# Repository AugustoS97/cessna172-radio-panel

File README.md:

# cessna-radio-panel

Radio panel for COM or NAV for a Cessna 172 to use with MSFS2020, XPlane and Prepar3D using the software MobiFlight.

# Repo contents

## Cessna-radio-stack-pcb
This folder contents the PCB design for the radio module. The design is the same for COM and NAV, it only changes on the frame. This PCB needs to be connected to the Arduino Mega using the Mega-pro-mini module designed in this repository. There is a GERBER folder to send the design to JLCPCB (www.jlcpcb.com) or you can ask me to buy it finished (augustosamuelhdezmartin@gmail.com).

To make this PCB you need this components (you can find the list in cessna172-radio-panel/Cesna-Radio-Stack-pcb/Docs/Cesna_Radio_Stack.csv):
- 4x Display 7 segments 0.36" 1 bit Common Cathode red (https://www.aliexpress.com/item/1005001852229452.html?spm=a2g0o.cart.0.0.44e13c00yVY6Ir&mp=1)
- 2x Display 7 segments 0.36" 4 bit Common Cathode red AS3161 (https://www.aliexpress.com/item/32673704841.html?spm=a2g0o.cart.0.0.44e13c00yVY6Ir&mp=1).
- 2x Rottary Encoder EC11 (https://es.aliexpress.com/item/1005002931777351.html?spm=a2g0o.cart.0.0.44e13c00yVY6Ir&mp=1) 
- 1x Button 8x8 (https://www.aliexpress.com/item/32467872702.html?spm=a2g0o.cart.0.0.44e13c00yVY6Ir&mp=1)
- 2x MAX7219 DIP24 (https://www.aliexpress.com/item/32874536319.html?spm=a2g0o.cart.0.0.44e13c00yVY6Ir&mp=1)
- 1x PinHeader 2x36 pins (https://www.aliexpress.com/item/33004522737.html?spm=a2g0o.cart.0.0.44e13c00yVY6Ir&mp=1)
- 8x 1k Resistor THT
- 7x 10nF Ceramic Capacitor THT
- 2x 150nF Ceramic Capacitor THT
- 2x 22uF Electrolitic Capcitor 16V

## Mega2560-pro-mini-radio
This folder contents the PCB design for the microcontroller. The design connects 2 NAV modules, 2 COM modules or 1 NAv and 1 COM modules. There is a GERBER folder to send the design to JLCPCB (www.jlcpcb.com) or you can ask me to buy it finished (augustosamuelhdezmartin@gmail.com).

To make this PCB you need this components (you can find the list in cessna172-radio-panel/Mega2560-pro-mini-radio/docs/Mega2560-pro-mini-radio.csv):
- 1x Mega 2650 Pro mini (https://www.aliexpress.com/item/1005001798708448.html?spm=a2g0o.cart.0.0.44e13c00yVY6Ir&mp=1)
- 3x PinHeader male 2x36 pins 2.54 mm (https://www.aliexpress.com/item/32993182990.html?spm=a2g0o.cart.0.0.44e13c00yVY6Ir&mp=1)
- 3x PinHeader Female 1x40 pins 2.54mm (https://www.aliexpress.com/item/32993182990.html?spm=a2g0o.cart.0.0.44e13c00yVY6Ir&mp=1)
- 2x IDC 2x20 pins 2.54mm Cable (https://www.aliexpress.com/item/33029492417.html?spm=a2g0o.cart.0.0.44e13c00yVY6Ir&mp=1): One for each module

## Frame Design
This folders contents the FreeCAD design for the exterior panel. It is based on the c172-xpndr design (https://github.com/kkr0kk/c172-xpndr), so it must be use with this Transponder and AutoPilot modules.

Also the 3D model are available in STL folder, so you can print this panels with 2 colors or you can also contact me to buy a finished panel (augustosamuelhdezmartin@gmail.com).

## Assembly 
Finallly, the COM panel is assembly as shown in the next picture.

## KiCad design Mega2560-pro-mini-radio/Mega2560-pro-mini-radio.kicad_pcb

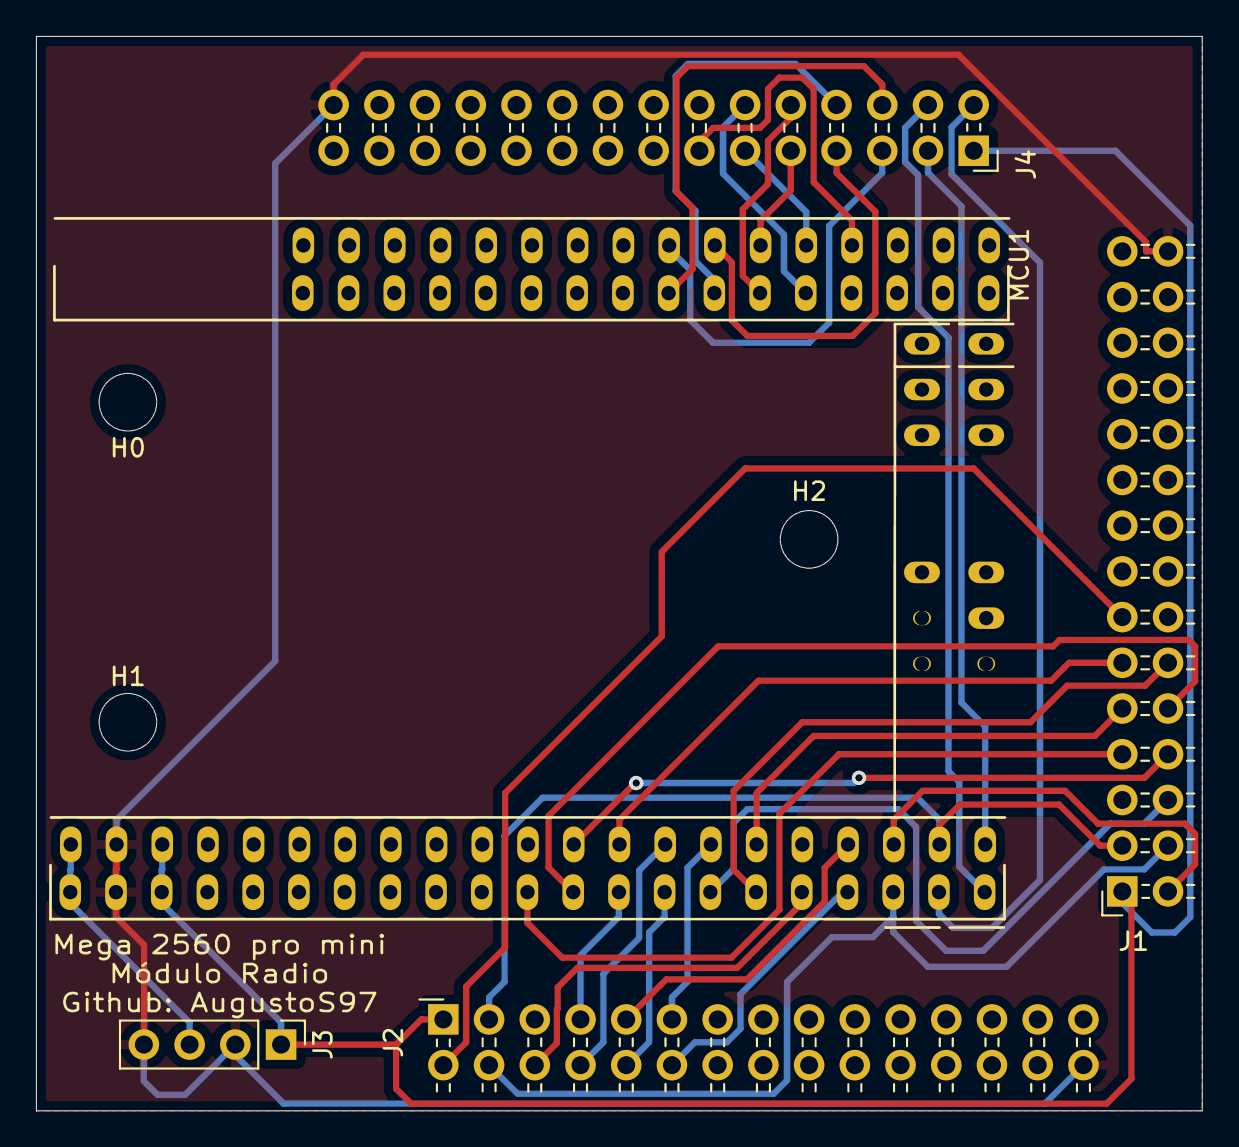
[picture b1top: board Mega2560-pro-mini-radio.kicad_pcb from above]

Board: 2 copper layers, 64.8 x 59.7 mm, 8 parts (0 on the bottom side), 33 nets.

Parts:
H0, H1, H2: MountingHole_3.2mm_M3
J1: COM_CONN; PinSocket_2x15_P2.54mm_Horizontal
J2: NAV_CONN; PinSocket_2x15_P2.54mm_Horizontal
J3: Power_Conn; PinHeader_1x04_P2.54mm_Vertical
J4: SW_CONN; PinSocket_2x15_P2.54mm_Horizontal
MCU1: Mega_Embebido; MEGA_Embebido

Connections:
+5V: J1.1, J2.1, J3.1, J4.1, MCU1.5, MCU1.6
ADF: J4.9, MCU1.53
AUX: J4.10, MCU1.54
A_COM_ENC_KHZ: J1.7, MCU1.22
A_COM_ENC_MHZ: J1.10, MCU1.24
A_NAV_ENC_KHZ: J2.7, MCU1.26
A_NAV_ENC_MHZ: J2.10, MCU1.28
BOTH: J4.4, MCU1.42
B_COM_ENC_KHZ: J1.8, MCU1.23
B_COM_ENC_MHZ: J1.11, MCU1.25
B_NAV_ENC_KHZ: J2.8, MCU1.27
B_NAV_ENC_MHZ: J2.11, MCU1.29
CLK: J1.3, J2.3, MCU1.39
COM1: J4.2, MCU1.40
COM2: J4.3, MCU1.41
COM_SWAP: J1.6, MCU1.30
CS_MAX: J1.4, J2.4, MCU1.38
DIN: J1.2, MCU1.37
DME: J4.8, MCU1.52
DOUT: J1.13, J2.2
GND: J1.30, J2.30, J3.2, J3.4, J4.30, MCU1.3, MCU1.4
I_led: J4.13, MCU1.57
MKR: J4.7, MCU1.51
M_led: J4.12, MCU1.56
NAV1: J4.5, MCU1.49
NAV2: J4.6, MCU1.50
NAV_SWAP: J2.6, MCU1.34
O_led: J4.11, MCU1.55
SW_COM_ENC_KHZ: J1.9, MCU1.31
SW_COM_ENC_MHZ: J1.12, MCU1.32
SW_NAV_ENC_KHZ: J2.9, MCU1.35
SW_NAV_ENC_MHZ: J2.12, MCU1.36
VCC: J3.3, MCU1.1, MCU1.2

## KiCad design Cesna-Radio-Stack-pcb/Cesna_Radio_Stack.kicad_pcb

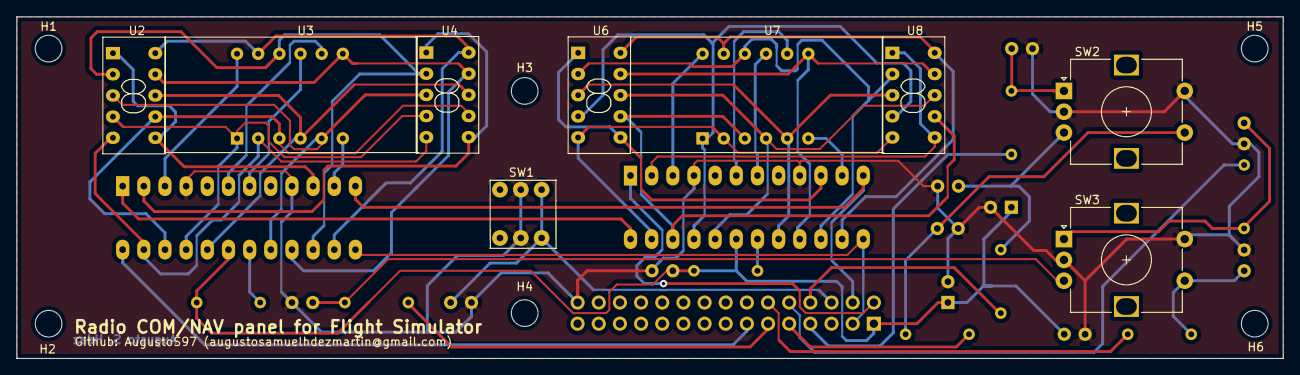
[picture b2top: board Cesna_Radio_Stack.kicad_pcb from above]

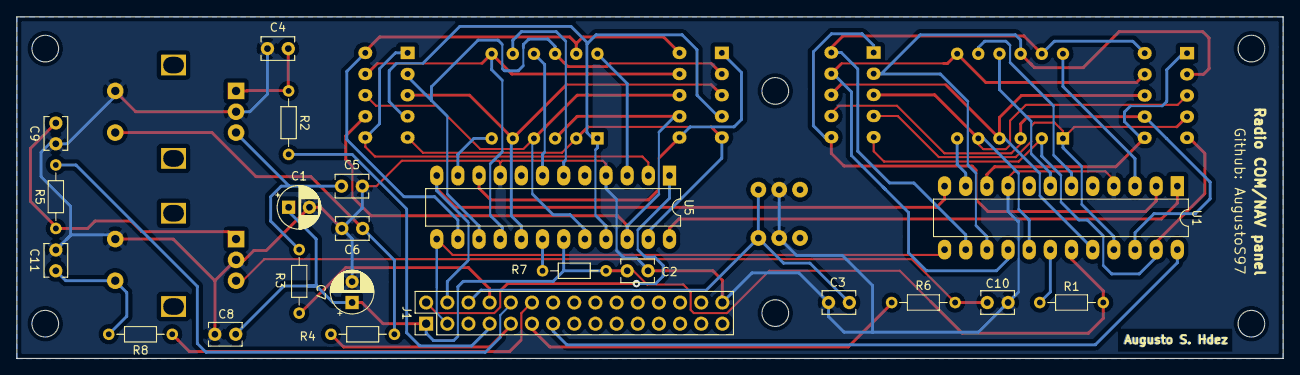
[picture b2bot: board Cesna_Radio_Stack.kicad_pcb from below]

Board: 2 copper layers, 152.0 x 41.0 mm, 37 parts (22 on the bottom side), 50 nets.

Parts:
C1, C7: 22uF; CP_Radial_D5.0mm_P2.50mm
C2, C8: 150nF; C_Disc_D3.8mm_W2.6mm_P2.50mm
C3, C4, C5, C6, C9, C10, C11: 10nF; C_Disc_D3.8mm_W2.6mm_P2.50mm
H1, H2, H3, H4, H5, H6: MountingHole_3.2mm_M3
J1: Conn_02x15_Odd_Even; PinHeader_2x15_P2.54mm_Vertical
R1, R2, R3, R4, R5, R6, R7, R8: 10k; R_Axial_DIN0204_L3.6mm_D1.6mm_P7.62mm_Horizontal
SW1: SW_COM; SPDT_8x8
SW2: NAV_ENC; RotaryEncoder_Alps_EC12E-Switch_Vertical_H20mm
SW3: COM_ENC; RotaryEncoder_Alps_EC12E-Switch_Vertical_H20mm
U1, U5: MAX7219; DIP-24_W7.62mm_LongPads
U2: HDSP-A153 NAV/COM_ACTV; 3161AS_7_Segmentos
U3: 3641-AS NAV/COM_ACTV; 3641-AS
U4: HDSP-A153 NAV/COM_ACTV_KHZ; 3161AS_7_Segmentos
U6: HDSP-A153 NAV/COM_STB; 3161AS_7_Segmentos
U7: 3641-AS NAV/COM_STB; 3641-AS
U8: HDSP-A153 NAV/COM_STB_KHZ; 3161AS_7_Segmentos

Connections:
+5V: C1.1, C2.1, C7.1, C8.1, J1.1, R1.2, R7.2, U1.19, U5.19
A_COM_ENC_KHZ: J1.7, R2.2
A_COM_ENC_MHZ: J1.10, R5.2
B_COM_ENC_KHZ: J1.8, R3.2
B_COM_ENC_MHZ: J1.11, R6.2
CLK: J1.3, U1.13, U5.13
COM_SWAP: C3.1, J1.6, SW1.1, SW1.4
CS_MAX: J1.4, U1.12, U5.12
DIN: J1.2, U5.1
DOUT: J1.13, U1.24
DOUT_MAX1: U1.1, U5.24
GND: C1.2, C2.2, C3.2, C4.1, C5.2, C6.2, C7.2, C8.2, C9.1, C10.2, C11.2, J1.30, SW1.2, SW1.5, SW2.C, SW2.S1, SW3.C, SW3.S1, U1.4, U1.9, U5.4, U5.9
unnamed: C4.2, R2.1, SW2.A
unnamed: C5.1, R3.1, SW2.B
unnamed: C6.1, R4.2, SW2.S2
unnamed: C9.2, R5.1, SW3.A
unnamed: C10.1, R6.1, SW3.B
unnamed: C11.1, R8.2, SW3.S2
unnamed: R1.1, U1.18
unnamed: R7.1, U5.18
unnamed: U1.2, U4.1, U4.6
unnamed: U1.3, U3.12
unnamed: U1.6, U3.8
unnamed: U1.7, U3.9
unnamed: U1.10, U2.1, U2.6
unnamed: U1.11, U3.6
unnamed: U1.14, U2.10, U3.11, U4.10
unnamed: U1.15, U2.2, U3.10, U4.2
unnamed: U1.16, U2.9, U3.7, U4.9
unnamed: U1.17, U2.3, U3.5, U4.3
unnamed: U1.20, U2.8, U3.4, U4.8
unnamed: U1.21, U2.4, U3.1, U4.4
unnamed: U1.22, U2.7, U3.3, U4.7
unnamed: U1.23, U2.5, U3.2, U4.5
unnamed: U5.2, U8.1, U8.6
unnamed: U5.3, U7.12
unnamed: U5.6, U7.8
unnamed: U5.7, U7.9
unnamed: U5.10, U6.1, U6.6
unnamed: U5.11, U7.6
unnamed: U5.14, U6.10, U7.11, U8.10
unnamed: U5.15, U6.2, U7.10, U8.2
unnamed: U5.16, U6.9, U7.7, U8.9
unnamed: U5.17, U6.3, U7.5, U8.3
unnamed: U5.20, U6.8, U7.4, U8.8
unnamed: U5.21, U6.4, U7.1, U8.4
unnamed: U5.22, U6.7, U7.3, U8.7
unnamed: U5.23, U6.5, U7.2, U8.5
SW_COM_ENC_KHZ: J1.9, R4.1
SW_COM_ENC_MHZ: J1.12, R8.1

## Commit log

2021-09-19 PCB Radio panel add.
2021-09-19 Mega2560 pcb add.
2021-09-25 En proceso de diseño del marco frontal impreso.
2021-09-28 PCB de ATMega modificada para permitir conectar los switches de control de los modulos COM.
2021-09-28 Añadidos los soportes para ATMega.
2021-10-10 Modificados los Frames de COM y NAV
2021-10-10 Modificados los STL de los marcos NAV y COM
2021-10-11 Renders añadidos.
